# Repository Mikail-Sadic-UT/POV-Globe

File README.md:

# POV Globe

A persistence-of-vision LED globe. A blade carrying a strip of SK9822 LEDs spins on a brushless motor; image columns are clocked out in sync with the motor's hall sensor so a stable spherical image hangs in mid-air.

---

## How It Works

A hall sensor feeds back the motor's rotation period. A timer divides that period across the number of angular columns and fires at that rate — each tick, the next column of image data is pushed out to the LEDs via DMA while the CPU stays free.

Three display modes:

| Mode | Description |
|------|-------------|
| Static image | Indexed image loaded from ROM or SD card |
| Animation | GIF streamed from SD card, double-buffered per rotation |
| Mic / VU meter | Electret mic drives a colour bar from hub to tip |

---

## Repository Layout

```
POV-Globe/
├── Firmware/     Code Composer Studio project (TM4C123GH6PM)
├── Hardware/     KiCad 9.0 PCB files
├── Mechanical/   Step files
├── Scripts/      Python image conversion tools
└── BOM.xlsx      Bill of materials
```

---

## Firmware

Targets the TI TM4C123GH6PM (Tiva C) using [Code Composer Studio](https://www.ti.com/tool/CCSTUDIO).

### Quick Start

1. Open the project in Code Composer Studio (`Firmware/src/`).
2. Make sure `main_sd.c` is the active entry point.
3. Connect the board and hit **Debug** — CCS flashes and starts execution.
4. Use the LCD buttons to navigate the menu, select content, and control the motor.

### Adding Content

**ROM image** (compiled into flash, no SD card needed):

```bash
cd Scripts
python globe_convert.py myimage.png
```

Move the output into `Firmware/src/Data/myimage/` and register the entry in `main_sd.c`. See [`Scripts/Documentation.md`](Scripts/Documentation.md) for details.

**SD card animation** (streamed at runtime):

```bash
python globe_convert_gif.py myanim.gif
```

Copy the `.bin` file to the SD card and register the palette entry in `main_sd.c`. See [`Scripts/Documentation.md`](Scripts/Documentation.md) for details.

### Docs

Detailed module documentation lives in `Firmware/src/Documentation/`:

- [`main_sd.md`](Firmware/src/Documentation/main_sd.md) — application architecture, display modes, init order
- [`Motor.md`](Firmware/src/Documentation/Motor.md) — PWM control, hall RPM capture, ramp state machine
- [`SK9822.md`](Firmware/src/Documentation/SK9822.md) — frame builders and wire format
- [`SSI-DMA.md`](Firmware/src/Documentation/SSI-DMA.md) — DMA pipeline and SPI setup

---

## Hardware

KiCad 9.0 is required to open the schematic and PCB files. All design files and documentation are inside the `Hardware/` folder.

---

## Scripts

| Script | Purpose |
|--------|---------|
| `globe_convert.py` | Converts an equirectangular image to C arrays for ROM or SD use |
| `globe_convert_gif.py` | Converts a GIF to a binary + palette for SD card streaming |
| `toBin.py` | Binary packing utility |

See [`Scripts/Documentation.md`](Scripts/Documentation.md) for full usage.

## Mechanical

See Mechanical Folder for STEP models and assembly. 
Youtube video:

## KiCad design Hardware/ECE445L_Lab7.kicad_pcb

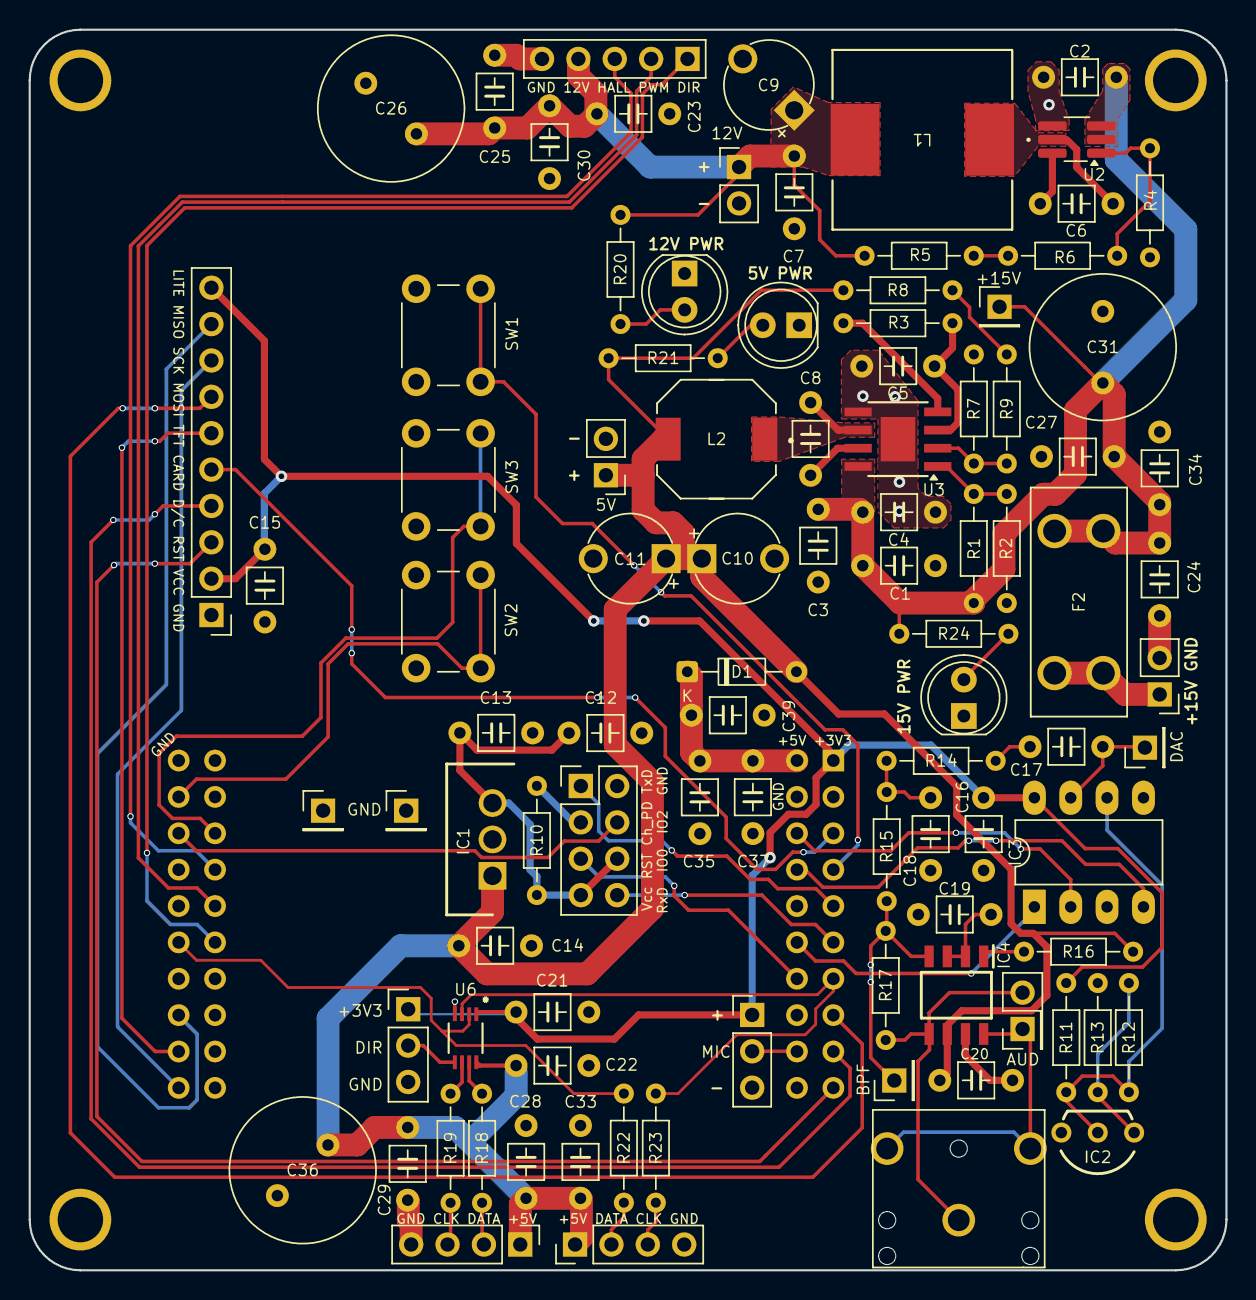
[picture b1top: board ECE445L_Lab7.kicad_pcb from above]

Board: 2 copper layers, 83.6 x 86.6 mm, 100 parts (1 on the bottom side), 63 nets.

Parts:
C1, C3, C7, C13, C14, C25, C27, C29, C37: 10uF; C_Axial_200mil
C2: 2.2uF; C_Axial_200mil
C4, C6, C8, C12, C16, C17, C20, C21, C22, C23, C24, C28, C35: 0.1uF; C_Axial_200mil
C5, C15, C19, C30, C33, C34, C39: 1uF; C_Axial_200mil
C9, C10, C11: 22uF; CP_Radial_Tantal200mil
C18: 10nF; C_Axial_200mil
C26, C31, C36: 680uF; C_Radial_D10.0mm_H20.0mm_P5.00mm
D1: Schottcky?; D_DO-34_SOD68_P7.62mm_Horizontal
D2, D3, D4: LED; LED_D5.0mm
F2: 3568; FUSE_3568
H1, H2, H3, H4: MountingHole_4_40
IC1: LM2937ET-3.3_NOPB; TO254P470X1028X1955-3P
IC2: LM4041CILPR; ti_LM4041CILPR
IC3: TLV5616; DIP-8_W7.62mm_LongPads
IC4: LM4890M_NOPB; ti_LM4890M_NOPB
J1: MIC; PinHeader_1x03_P2.54mm_Vertical
J2: PWR_IN; PinHeader_1x02_P2.54mm_Vertical
J3, J7: LED; PinHeader_1x04_P2.54mm_Vertical
J4: Motor; PinHeader_1x05_P2.54mm_Vertical
J5: AudioJack; Jack_3.5mm_CUI_SJ1-3523N_Horizontal
J8: 12V; PinHeader_1x02_P2.54mm_Vertical
J9: 5V; PinHeader_1x02_P2.54mm_Vertical
JP1: Jumper_3_Open; PinHeader_1x03_P2.54mm_Vertical
L1: 15uH; IFDC5050HZER150M
L2: 3.3uH; 1217AS
LS1: Speaker; PinHeader_2x01_P2.54mm_Vertical
R1: 56k; R_Axial_DIN0204_L3.6mm_D1.6mm_P7.62mm_Horizontal
R2, R4, R10, R13, R16, R17: 10k; R_Axial_DIN0204_L3.6mm_D1.6mm_P7.62mm_Horizontal
R3: 100k; R_Axial_DIN0204_L3.6mm_D1.6mm_P7.62mm_Horizontal
R5, R8: 120k; R_Axial_DIN0204_L3.6mm_D1.6mm_P7.62mm_Horizontal
R6: 20k; R_Axial_DIN0204_L3.6mm_D1.6mm_P7.62mm_Horizontal
R7: 22k; R_Axial_DIN0204_L3.6mm_D1.6mm_P7.62mm_Horizontal
R9: 3.9k; R_Axial_DIN0204_L3.6mm_D1.6mm_P7.62mm_Horizontal
R11, R15: 2k; R_Axial_DIN0204_L3.6mm_D1.6mm_P7.62mm_Horizontal
R12: 47k; R_Axial_DIN0204_L3.6mm_D1.6mm_P7.62mm_Horizontal
R14: 30k; R_Axial_DIN0204_L3.6mm_D1.6mm_P7.62mm_Horizontal
R18, R19, R22, R23: 51; R_Axial_DIN0204_L3.6mm_D1.6mm_P7.62mm_Horizontal
R20: 5.1k; R_Axial_DIN0204_L3.6mm_D1.6mm_P7.62mm_Horizontal
R21: 1500; R_Axial_DIN0204_L3.6mm_D1.6mm_P7.62mm_Horizontal
R24: 6.5k; R_Axial_DIN0204_L3.6mm_D1.6mm_P7.62mm_Horizontal
SW1: SW1; SW_PUSH_6mm
SW2: SW2; SW_PUSH_6mm
SW3: SW3; SW_PUSH_6mm
TP1, TP2, TP5, TP6, TP7: TestPoint; PinHeader_1x01_P2.54mm_Vertical
U1: EK-TM4C123GXL; ti_EKTM4C123GXL
U2: LMR51635XFDDCR; TSOT-23-6_HandSoldering
U3: TPS56628DDAR; TI_SO-PowerPAD-8
U4: ESP8266-1; PinHeader_2x04_P2.54mm_Vertical
U5: Adafruit ST7735R; PinHeader_1x10_P2.54mm_Vertical
U6: 74AXP2T45DCH

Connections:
+1V5: IC2.2, IC3.6 (REF), R11.2, R12.1
+3V3: C15.1, C16.2, C21.2, IC3.8 (VDD), J1.1, JP1.1 (A), R11.1, U1.J1_1 (+3.3V), U5.2 (VCC), U5.10 (LITE), U6.1 (VCCA)
+5V: C10.1, C11.1, C14.1, C20.2, C22.2, C28.2, C29.2, C33.2, C36.1, D1.2 (A), IC1.1 (INPUT), IC4.6 (VDD), J3.1, J7.1, J9.1, L2.2, R8.1, R16.2, R21.1, U6.8 (VCCB)
+12V: C7.1, C9.1, C23.2, C25.2, C26.1, C30.2, J4.4, J8.1, L1.2, R5.1, R20.1
+15V: C1.1, C2.1, C3.1, C4.1, C24.2, C27.2, C31.1, C34.2, F2.2, F2.4, R1.2, R24.1, TP1.1, U2.2 (EN), U2.3 (VIN), U3.8 (VIN)
/Lab7_Output/VO1: IC4.5 (VO_1), J5.S (sleeve), LS1.2, R17.1
/Lab7_Output/VO2: IC4.8 (VO2), J5.R (ring), J5.T (tip), LS1.1
/Lab7_power/123.9k: R7.1, R9.2, U3.2 (VFB)
/Lab7_power/140k: R4.1, R6.2, U2.1 (FB)
/Lab7_wifi/WIFI_3V3: C12.1, C13.1, IC1.3 (OUTPUT), R10.1, U4.2 (GPIO0), U4.8 (Vcc)
/PA2: U1.J2_10 (PA2), U5.8 (SCK)
/PA3: U1.J2_9 (PA3), U5.6 (TFT_CS)
/PA4: U1.J2_8 (PA4), U5.9 (MISO)
/PA5: U1.J1_8 (PA5), U5.7 (MOSI)
/PA6: U1.J1_9 (PA6), U5.4 (D/C)
/PA7: U1.J1_10 (PA7), U5.3 (RESET)
/PB0: U1.J1_3 (PB0), U5.5 (CARD_CS)
/PB1: SW1.2, U1.J1_4 (PB1)
/PB2: SW2.2, U1.J2_2 (PB2)
/PB3: SW3.2, U1.J4_3 (PB3)
/PB4: R23.1, U1.J1_7 (PB4), U6.3 (2A)
/PB7: R22.2, U1.J2_6 (PB7), U6.2 (1A)
/PC4: J4.3, U1.J4_4 (PC4)
/PC5: J4.2, U1.J4_5 (PC5)
/PC6: J4.1, U1.J4_6 (PC6)
/PD0: IC3.2 (SCLK), U1.J3_3 (PD0)
/PD1: IC3.4 (FS), U1.J3_4 (PD1)
/PD3: IC3.1 (DIN), U1.J3_6 (PD3)
/PE0: U1.J2_3 (PE0), U4.3 (GPIO2)
/PE1: U1.J3_7 (PE1), U4.7 (Reset)
/PE3: J1.2, U1.J3_9 (PE3)
/PE4: U1.J1_5 (PE4), U4.5 (TxD)
/PE5: U1.J1_6 (PE5), U4.1 (RxD)
GND: C1.2, C2.2, C3.2, C4.2, C5.2, C7.2, C9.2, C10.2, C11.2, C12.2, C13.2, C14.2, C15.2, C16.1, C18.1, C19.1, C20.1, C21.1, C22.1, C23.1, C24.1, C25.1, C26.2, C27.1, C28.1, C29.1, C30.1, C31.2, C33.1, C34.1, C35.1, C36.2, C37.1, C39.1, D2.1 (K), D3.1 (K), D4.1 (K), IC1.2 (GND), IC2.3, IC3.3 (~CS), IC3.5 (AGND), IC4.7 (GND), J1.3, J2.2, J3.4, J4.5, J7.4, J8.2, J9.2, JP1.3 (B), R2.2, R4.2, R7.2, R13.2, SW1.1, SW2.1, SW3.1, TP2.1, TP5.1, U1.J2_1 (GND), U1.J3_2 (GND), U2.4 (GND), U3.5 (GND), U3.9 (GND), U4.4 (GND), U5.1 (GND), U6.4 (GND)
unnamed: C17.2, R14.1
unnamed: C18.2, R14.2, R15.1
unnamed: C35.2, C37.2, C39.2, D1.1 (K), U1.J3_1 (+VBUS)
unnamed: D2.2 (A), R20.2
unnamed: D3.2 (A), R21.2
unnamed: D4.2 (A), R24.2
unnamed: IC2.1, R12.2, R13.1
unnamed: C17.1, IC3.7 (OUT), TP6.1
unnamed: C19.2, IC4.2 (BYPASS), IC4.3 (+IN)
unnamed: IC4.4 (-IN), R15.2, R17.2, TP7.1
unnamed: IC4.1 (~SHUTDOWN), R16.1
unnamed: F2.1, F2.3, J2.1
unnamed: J3.2, R18.1
unnamed: J3.3, R19.2
unnamed: J7.2, R22.1
unnamed: J7.3, R23.2
unnamed: JP1.2 (C), U6.5 (DIR)
unnamed: R5.2, R6.1
unnamed: R8.2, R9.1
unnamed: C6.1, U2.6 (CB)
unnamed: C6.2, L1.1, U2.5 (SW)
unnamed: R1.1, R2.1, U3.1 (EN)
unnamed: R3.1, U3.4 (PG)
unnamed: C8.2, L2.1, U3.6 (SW)
unnamed: C8.1, U3.7 (VBST)
unnamed: C5.1, R3.2, U3.3 (VREG5)
unnamed: R10.2, U4.6 (Ch_PD)
unnamed: R18.2, U6.7 (1B)
unnamed: R19.1, U6.6 (2B)

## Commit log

2026-06-15 HW+FW
2026-06-15 README
2026-06-15 Re-ordered
2026-06-16 Added Mechanical Files
2026-06-16 Update README with demo video and mechanical info
    Added demo video section and mechanical folder reference.
2026-06-16 Clean up demo video section in README
    Removed old demo video section and HTML formatting.
